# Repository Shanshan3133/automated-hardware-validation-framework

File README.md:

# Automated Hardware Validation Framework

A portfolio project combining a protected 5 V buck-converter PCB with a Python automated validation bench. It demonstrates PCB design, instrument automation, fault injection, safety interlocks, data logging, and CI-style reporting—the day-to-day concerns of hardware validation and systems-integration engineering.

> **Engineering status:** the software framework is operational. The KiCad 10 schematic passes ERC with zero violations, and the routed PCB passes DRC with zero violations and zero unconnected pads. This is still an engineering prototype, not a fabrication release: land patterns, thermal-via design, compensation, derating, enclosure constraints, and schematic/PCB parity need independent review.

## PCB preview

## KiCad schematic

The editable source is `hardware/protected_buck.kicad_sch`; its generated PDF is included for design review. KiCad 10.0.6 reports zero ERC errors and zero ERC warnings, and the automated parity check matches all 88 schematic pins to 88 PCB pads.

## Electrical architecture

This review overview explicitly separates the TPS26600 `RTN` domain from `SYSTEM_GND`, shows the required 10 nF BOOT-to-PH capacitor, and identifies the protected DAQ signals.

The DUT uses a TPS26600 eFuse front end and a TPS5431 asynchronous buck stage. It targets 8–18 V input, regulated 5 V output, and a 1 A continuous validation load. The fixture connector exposes divided VIN/VOUT measurements, active-low fault status, shutdown control, and current-monitor signals.

## System architecture

```mermaid
flowchart LR
    PY[Python test runner] -->|SCPI / USB| PSU[Programmable supply]
    PSU --> DUT[Protected 5 V buck DUT]
    DUT --> LOAD[Electronic load]
    DUT -->|VIN and VOUT| ADC[MCP3008 ADC]
    DUT -->|FLT and SHDN| GPIO[Raspberry Pi GPIO]
    ADC --> PI[Raspberry Pi]
    GPIO --> PI
    PI --> PY
    PY --> DATA[CSV and JSON results]
    DATA --> REPORT[CI-style HTML report]
```

All test logic depends on an abstract `Bench` interface. The same suite runs against a deterministic behavioral simulator in CI or against physical SCPI instruments and Raspberry Pi I/O in the lab.

## Automated test coverage

| Test | Stimulus | Measurement | Pass criterion |
|---|---|---|---|
| Line regulation | VIN from 8 V to 18 V | VOUT | 5.0 V ±3% |
| Load regulation | Load from 0 A to 1 A | VOUT | 5.0 V ±3% |
| Output ripple | 2,000 samples at 10 MS/s | Robust Vpp | <50 mVpp |
| UVLO rising | VIN from 6 V to 9 V | Turn-on threshold | 7.1–7.9 V |
| OVP rising | VIN from 17 V to 21 V | Fault threshold | 18.4–19.6 V |
| Overcurrent trip | Load from 0.5 A to 1.8 A | Fault threshold | 1.35–1.65 A |

The MCP3008 measures DC rails and low-frequency behavior. The physical ripple test deliberately requests a 10 MS/s window through a SCPI oscilloscope adapter because a low-speed ADC cannot characterize the TPS5431's 500 kHz switching ripple. Use a bandwidth-limited scope measurement with a short ground spring and verify the scope's actual acquisition settings.

## Example validation result

```text
PASS   Line regulation: VOUT range 4.995–5.011 V
PASS   Load regulation: VOUT range 4.992–5.010 V
PASS   Output ripple: Ripple 30.3 mVpp; mean 4.993 V
PASS   UVLO rising: Turn-on detected at 7.50 V
PASS   OVP rising: Trip detected at 19.05 V
PASS   Overcurrent trip: Trip detected at 1.500 A
```

View the self-contained [HTML report with measurement plots](artifacts/report.html), [machine-readable results](artifacts/results.json), and individual CSV files in `artifacts/`.

Fault injection verifies that real specification failures are detected:

```powershell
python -m validation.cli run --backend sim --fault high-ripple --output artifacts-failing
```

This produces a failing 91.3 mVpp result and a nonzero process exit code suitable for CI gating.

## Repository layout

```text
hardware/
  protected_buck.kicad_pro      KiCad project
  protected_buck.kicad_sch      complete editable schematic; ERC clean
  protected_buck.kicad_pcb      routed two-layer PCB; DRC clean
  protected_buck.dsn/.ses       reproducible Specctra routing exchange
  protected_buck_3d.png         generated 3D preview
  protected_buck_layout.pdf     copper-layer review PDF
  protected_buck_schematic.pdf  schematic review PDF
  BOM.csv                       preliminary bill of materials
  DESIGN.md                     calculations and layout rationale
  BRINGUP.md                    controlled first-power procedure
validation/
  instruments.py                bench abstraction
  simulator.py                  deterministic behavioral DUT model
  real_bench.py                 PyVISA supply/load/scope, MCP3008, and GPIO adapters
  test_cases.py                 validation procedures and limits
  report.py                     CSV, JSON, and HTML reporting
tests/                          software unit tests
scripts/generate_board.py       reproducible KiCad PCB generator
scripts/finalize_route.py       imports routing session and finalizes reviewed nets
scripts/generate_schematic_modern.py  reproducible KiCad 10 schematic generator
scripts/check_design_parity.py  checks every schematic pin against its PCB pad net
.github/workflows/              simulated validation workflow
```

## Quick start

Simulation requires Python 3.10+ and no third-party runtime packages:

```powershell
python -m validation.cli run --backend sim --output artifacts
python -m unittest discover -s tests -v
```

Open `artifacts/report.html` after the run.

## Physical bench setup

```powershell
pip install -e ".[raspberry-pi]"
Copy-Item validation/real_bench.example.json bench.json
python -m validation.cli run --backend real --config bench.json --output artifacts-real
```

Before using the real backend:

1. Verify SCPI resource names and commands against the exact instruments.
2. Calibrate every ADC divider and verify the oscilloscope probe ratio, bandwidth limit, and channel.
3. Install an independent physical emergency-off.
4. Configure the supply limit to 2 A or less and OVP to 22 V.
5. Complete [BRINGUP.md](hardware/BRINGUP.md) with the first run attended.

The real-bench factory rejects configurations above the 2 A project safety ceiling before opening hardware resources. `safe_shutdown()` removes the electronic load and source output if a test raises an exception.

## Hardware design targets

| Characteristic | Target |
|---|---:|
| Operating input range | 8–18 V |
| Output voltage | 5.0 V ±3% |
| Validation load | 1.0 A continuous |
| Automated ripple screen | <50 mVpp |
| UVLO rising threshold | 7.5 V ±0.4 V |
| OVP rising threshold | 19.0 V ±0.6 V |
| Current-limit trip | 1.50 A ±0.15 A |

See [DESIGN.md](hardware/DESIGN.md) for calculations, [VALIDATION_STATUS.md](hardware/VALIDATION_STATUS.md) for the exact engineering status, and [ROUTING_CHECKLIST.md](hardware/ROUTING_CHECKLIST.md) for the post-routing review gates.

## Before fabrication

- Verify exposed-pad thermal-via patterns with the PCB manufacturer.
- Recheck compensation, bootstrap, current-limit mode, component derating, and fault behavior against the ordered part numbers.
- Add and mechanically validate mounting holes and enclosure clearances.
- Run schematic/PCB parity checks, inspect the autorouted geometry manually, and complete an independent engineering review.
- Assemble one prototype and complete the controlled bring-up and physical validation plan.

This repository is an engineering portfolio artifact and learning platform. It is not a certified power product or production manufacturing release.

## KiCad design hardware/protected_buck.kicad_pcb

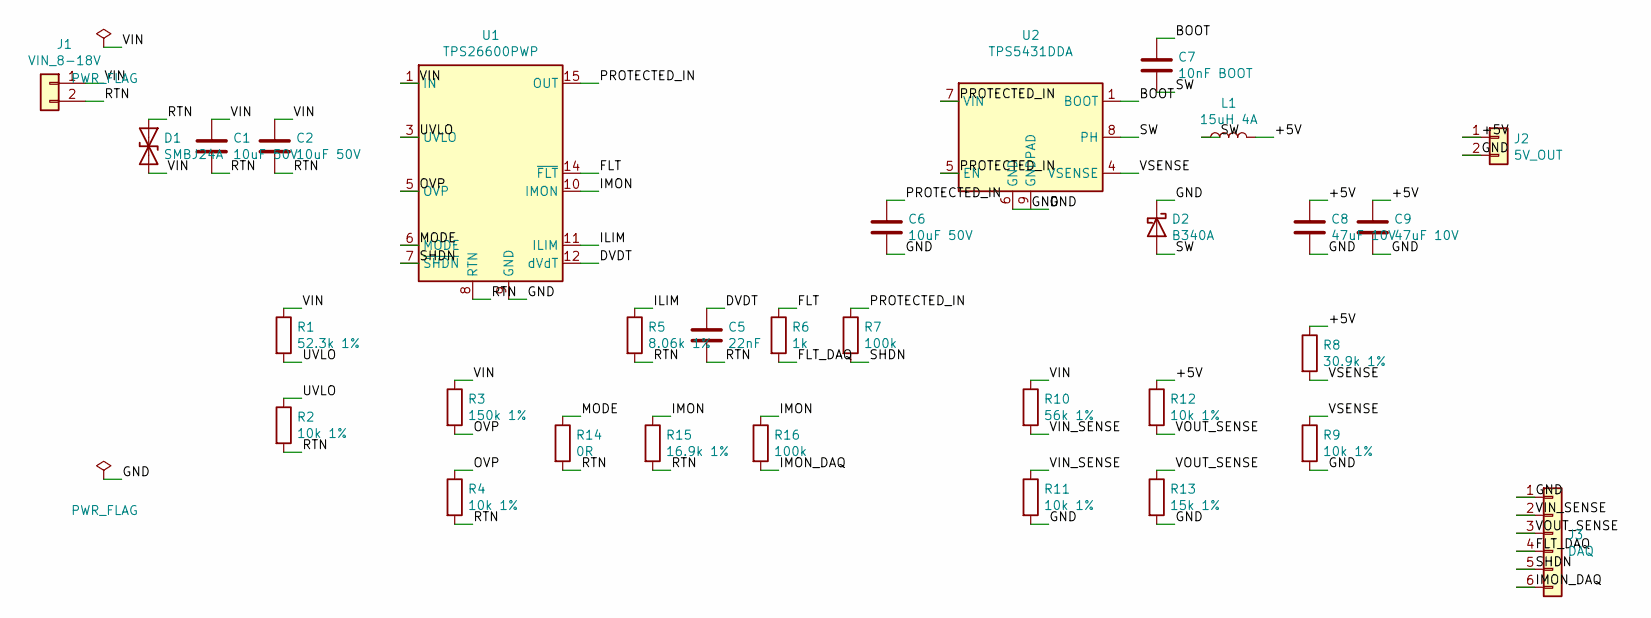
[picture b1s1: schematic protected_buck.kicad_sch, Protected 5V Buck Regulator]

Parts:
C1, C2, C6: 10uF 50V; C_1210_3225Metric
C5: 22nF; C_0603_1608Metric
C7: 10nF BOOT; C_0603_1608Metric
C8, C9: 47uF 10V; C_1210_3225Metric
D1: SMBJ24A; D_SMB
D2: B340A; D_SMA
J1: VIN_8-18V; TerminalBlock_Phoenix_MKDS-1,5-2_1x02_P5.00mm_Horizontal
J2: 5V_OUT; TerminalBlock_Phoenix_MKDS-1,5-2_1x02_P5.00mm_Horizontal
J3: DAQ; PinHeader_1x06_P2.54mm_Vertical
L1: 15uH 4A; L_10.4x10.4_H4.8
R1: 52.3k 1%; R_0603_1608Metric
R2, R4, R9, R11, R12: 10k 1%; R_0603_1608Metric
R3: 150k 1%; R_0603_1608Metric
R5: 8.06k 1%; R_0603_1608Metric
R6: 1k; R_0603_1608Metric
R7, R16: 100k; R_0603_1608Metric
R8: 30.9k 1%; R_0603_1608Metric
R10: 56k 1%; R_0603_1608Metric
R13: 15k 1%; R_0603_1608Metric
R14: 0R; R_0603_1608Metric
R15: 16.9k 1%; R_0603_1608Metric
U1: TPS26600PWP; HTSSOP-16-1EP_4.4x5mm_P0.65mm_EP3.4x5mm_Mask2.66x2.46mm
U2: TPS5431DDA; TI_SO-PowerPAD-8

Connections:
+5V: C8.1, C9.1, J2.1, L1.2, R8.1, R12.1; also elsewhere on the board
BOOT: C7.1, U2.1 (BOOT)
DVDT: C5.1, U1.12 (dVdT)
FLT: R6.1, U1.14 (~FLT)
FLT_DAQ: J3.4, R6.2
GND: C6.2, C8.2, C9.2, D2.1 (K), J2.2, J3.1, R9.2, R11.2, R13.2, U1.9 (GND), U2.6 (GND), U2.9 (GNDPAD); also elsewhere on the board
ILIM: R5.1, U1.11 (ILIM)
IMON: R15.1, R16.1, U1.10 (IMON)
IMON_DAQ: J3.6, R16.2
MODE: R14.1, U1.6 (MODE)
OVP: R3.2, R4.1, U1.5 (OVP)
PROTECTED_IN: C6.1, R7.1, U1.15 (OUT), U1.16 (OUT), U2.5 (EN), U2.7 (VIN); also elsewhere on the board
RTN: C1.2, C2.2, C5.2, D1.1 (A1), J1.2, R2.2, R4.2, R5.2, R14.2, R15.2, U1.8 (RTN), U1.17 (RTN)
SHDN: J3.5, R7.2, U1.7 (~SHDN)
SW: C7.2, D2.2 (A), L1.1, U2.8 (PH)
UVLO: R1.2, R2.1, U1.3 (UVLO)
VIN: C1.1, C2.1, D1.2 (A2), J1.1, R1.1, R3.1, R10.1, U1.1 (IN), U1.2 (IN); also elsewhere on the board
VIN_SENSE: J3.2, R10.2, R11.1
VOUT_SENSE: J3.3, R12.2, R13.1
VSENSE: R8.2, R9.1, U2.4 (VSENSE)

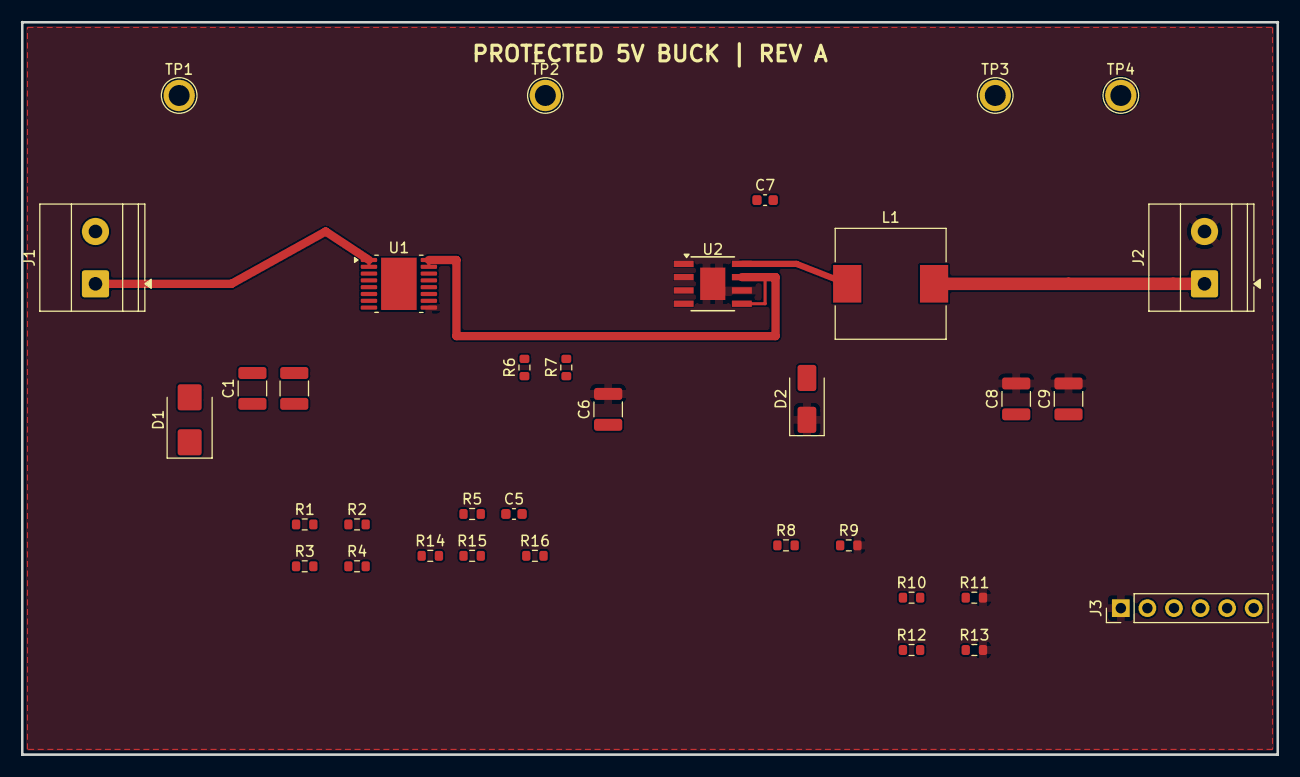
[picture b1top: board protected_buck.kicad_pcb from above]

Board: 2 copper layers, 120.0 x 70.0 mm, 35 parts (0 on the bottom side), 20 nets.

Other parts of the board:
TP1: VIN; TestPoint_Plated_Hole_D2.0mm
TP2: PROTECTED_IN; TestPoint_Plated_Hole_D2.0mm
TP3: +5V; TestPoint_Plated_Hole_D2.0mm
TP4: GND; TestPoint_Plated_Hole_D2.0mm

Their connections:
+5V: TP3.1; also elsewhere on the board
GND: TP4.1; also elsewhere on the board
PROTECTED_IN: TP2.1; also elsewhere on the board
VIN: TP1.1; also elsewhere on the board

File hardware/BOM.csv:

Reference,Qty,Value,Description,Footprint
U1,1,TPS26600PWPR,60 V 2 A eFuse with UVLO OVP ILIM,Package_SO:HTSSOP-16-1EP_4.4x5mm_P0.65mm
U2,1,TPS5431DDA,23 V 3 A 500 kHz asynchronous buck,Package_SO:TI_SO-PowerPAD-8_ThermalVias
D1,1,SMBJ24A,Input transient suppressor,Diode_SMD:D_SMB
D2,1,B340A,3 A 40 V Schottky catch diode,Diode_SMD:D_SMA
L1,1,15uH 4A,Shielded power inductor,Inductor_SMD:L_10.4x10.4_H4.8
C1 C2,2,10uF 50V,Input ceramic capacitor,Capacitor_SMD:C_1210_3225Metric
C5,1,22nF,eFuse output slew control to RTN,Capacitor_SMD:C_0603_1608Metric
C6,1,10uF 50V,Protected-input ceramic capacitor,Capacitor_SMD:C_1210_3225Metric
C7,1,10nF,TPS5431 BOOT-to-PH bootstrap capacitor,Capacitor_SMD:C_0603_1608Metric
C8 C9,2,47uF 10V,Output ceramic capacitor,Capacitor_SMD:C_1210_3225Metric
R1,1,52.3k 1%,UVLO divider upper,Resistor_SMD:R_0603_1608Metric
R2,1,10k 1%,UVLO divider lower to RTN,Resistor_SMD:R_0603_1608Metric
R3,1,150k 1%,OVP divider upper,Resistor_SMD:R_0603_1608Metric
R4,1,10k 1%,OVP divider lower to RTN,Resistor_SMD:R_0603_1608Metric
R5,1,8.06k 1%,Approximately 1.5 A eFuse limit,Resistor_SMD:R_0603_1608Metric
R6,1,1k,FLT series protection; fixture provides 3.3 V pull-up,Resistor_SMD:R_0603_1608Metric
R7,1,100k,SHDN fail-safe pull-up; drive with open drain,Resistor_SMD:R_0603_1608Metric
R8,1,30.9k 1%,5 V feedback upper,Resistor_SMD:R_0603_1608Metric
R9,1,10k 1%,5 V feedback lower,Resistor_SMD:R_0603_1608Metric
R14,1,0R,MODE to RTN for current-limit auto-retry,Resistor_SMD:R_0603_1608Metric
R15,1,16.9k 1%,IMON programming resistor to RTN,Resistor_SMD:R_0603_1608Metric
R16,1,100k,IMON ADC fault-current limiting series resistor,Resistor_SMD:R_0603_1608Metric
J1 J2,2,2-pin 5.08mm,Power terminal block,TerminalBlock_Phoenix:TerminalBlock_Phoenix_MKDS-1,5-2_1x02_P5.00mm_Horizontal
J3,1,1x06,DAQ header: GND VIN_SENSE VOUT_SENSE FLT_DAQ SHDN IMON_DAQ,Connector_PinHeader_2.54mm:PinHeader_1x06_P2.54mm_Vertical
TP1 TP2 TP3 TP4,4,Test point,VIN PROTECTED_IN VOUT GND,TestPoint:TestPoint_Plated_Hole_D2.0mm
R10 R11,2,56k / 10k 1%,VIN ADC divider,Resistor_SMD:R_0603_1608Metric
R12 R13,2,10k / 15k 1%,VOUT ADC divider,Resistor_SMD:R_0603_1608Metric
